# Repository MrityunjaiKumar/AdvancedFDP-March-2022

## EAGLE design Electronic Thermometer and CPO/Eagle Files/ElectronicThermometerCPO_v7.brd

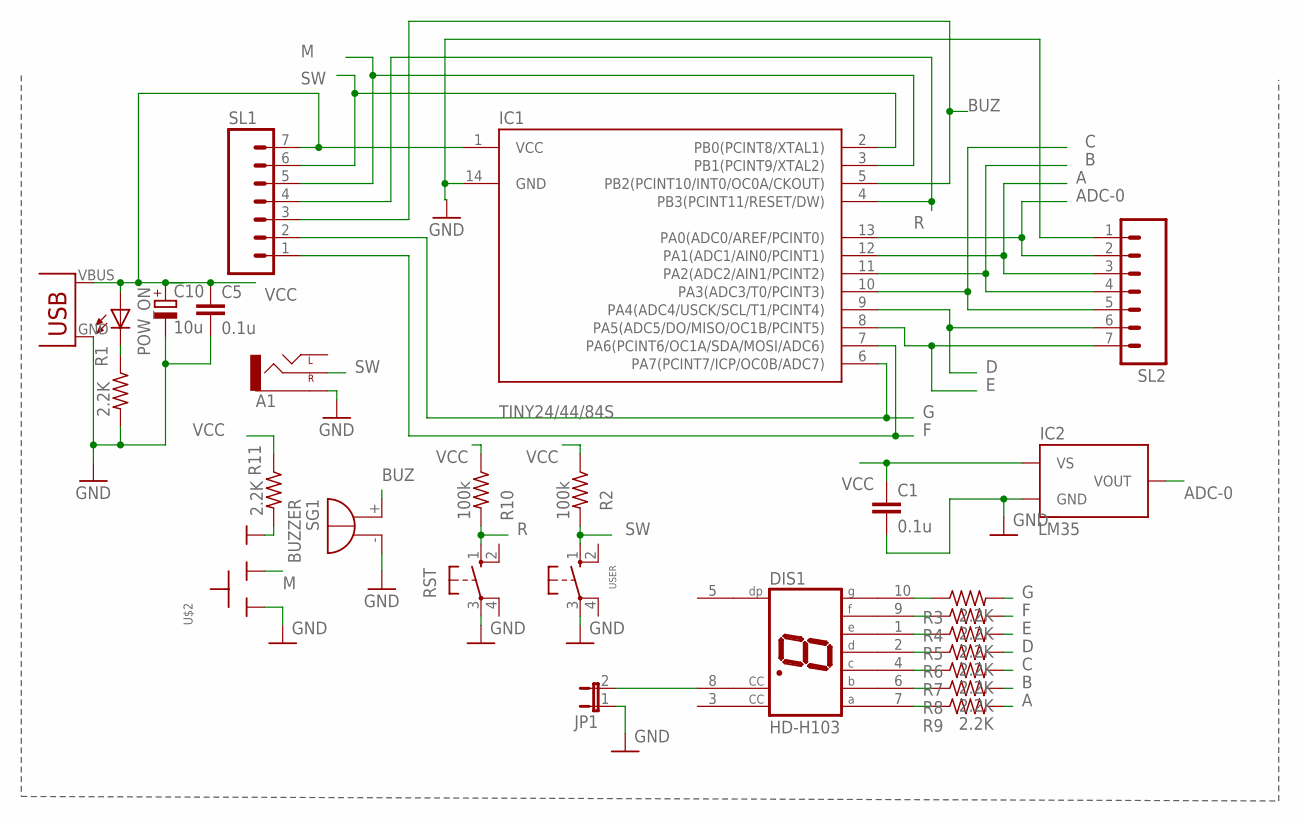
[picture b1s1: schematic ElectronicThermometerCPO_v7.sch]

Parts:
A1: AUDIO-JACKPTH; AUDIO-JACK
C1, C5: 0.1u; C0805
C10: 10u; B/3528-21R
DIS1: HD-H103; HDSP-M
IC1: TINY24/44/84S; SOIC14
IC2: LM35; TO92
JP1: JP1E; JP1
POW_ON: LED3MM
R1, R3, R4, R5, R6, R7, R8, R9, R11: 2.2K; 0207/10
R2, R10: 100k; 0207/10
RST: 10-XX; B3F-10XX
SG1: BUZZER; F/TMB
SL1, SL2: M07; 07P
U$1: USB(POWER)
U$2: SLIDESWITCH-BIG; BIGSWITCH
USER: 40-XX; B3F-40XX

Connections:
A: IC1.12 (PA1(ADC1/AIN0/PCINT1)), R9.2, SL2.3
ADC-0: IC1.13 (PA0(ADC0/AREF/PCINT0)), IC2.VOUT, SL2.2
B: IC1.11 (PA2(ADC2/AIN1/PCINT2)), R8.2, SL2.4
BUZ: IC1.5 (PB2(PCINT10/INT0/OC0A/CKOUT)), SG1.+, SL1.3
C: IC1.10 (PA3(ADC3/T0/PCINT3)), R7.2, SL2.5
D: IC1.9 (PA4(ADC4/USCK/SCL/T1/PCINT4)), R6.2, SL2.6
E: IC1.8 (PA5(ADC5/DO/MISO/OC1B/PCINT5)), R5.2, SL2.7
F: IC1.7 (PA6(PCINT6/OC1A/SDA/MOSI/ADC6)), R4.2, SL1.1
G: IC1.6 (PA7(PCINT7/ICP/OC0B/ADC7)), R3.2, SL1.2
GND: A1.SLEEVE, C1.2, C5.2, C10.-, IC1.14 (GND), IC2.GND, JP1.1, R1.2, RST.3, SG1.-, SL2.1, U$1.GND, U$2.1, USER.3
M: IC1.3 (PB1(PCINT9/XTAL2)), SL1.5, U$2.2
unnamed: POW_ON.K (C), R1.1
unnamed: DIS1.8 (CC), JP1.2
unnamed: DIS1.10 (G), R3.1
unnamed: DIS1.9 (F), R4.1
unnamed: R11.2, U$2.3
unnamed: DIS1.1 (E), R5.1
unnamed: DIS1.2 (D), R6.1
unnamed: DIS1.4 (C), R7.1
unnamed: DIS1.6 (B), R8.1
unnamed: DIS1.7 (A), R9.1
R: IC1.4 (PB3(PCINT11/RESET/DW)), R10.2, RST.1 (S), SL1.4
SW: A1.RING (RIGHT), IC1.2 (PB0(PCINT8/XTAL1)), R2.2, SL1.6, USER.1 (S)
VCC: C1.1, C5.1, C10.+, IC1.1 (VCC), IC2.VS, POW_ON.A, R2.1, R10.1, R11.1, SL1.7, U$1.VBUS (VCC)

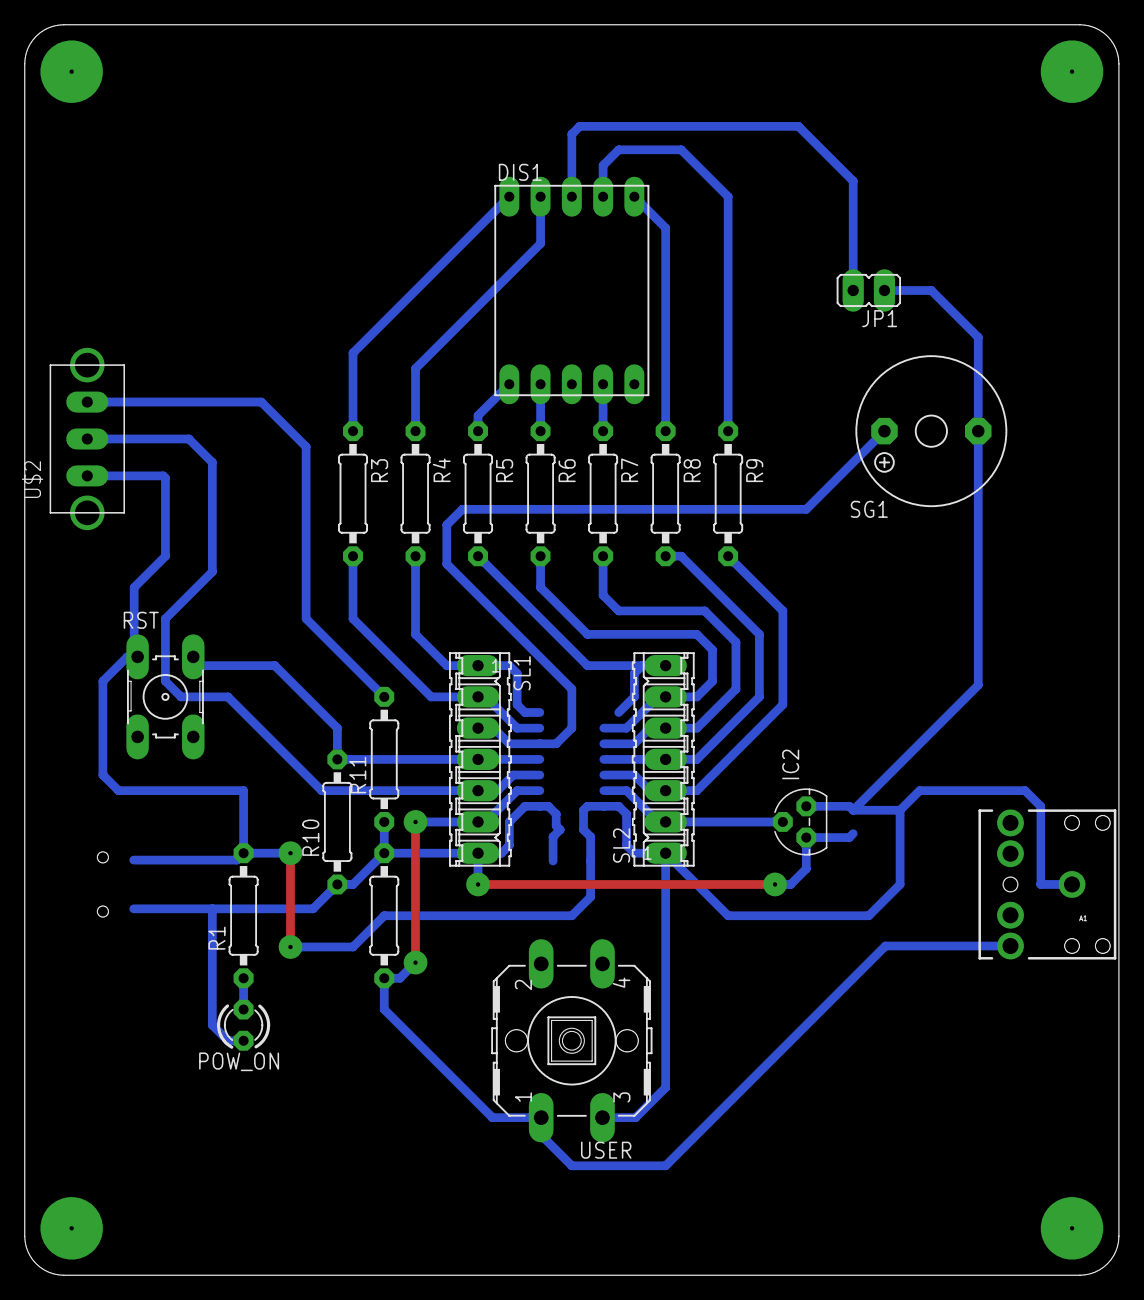
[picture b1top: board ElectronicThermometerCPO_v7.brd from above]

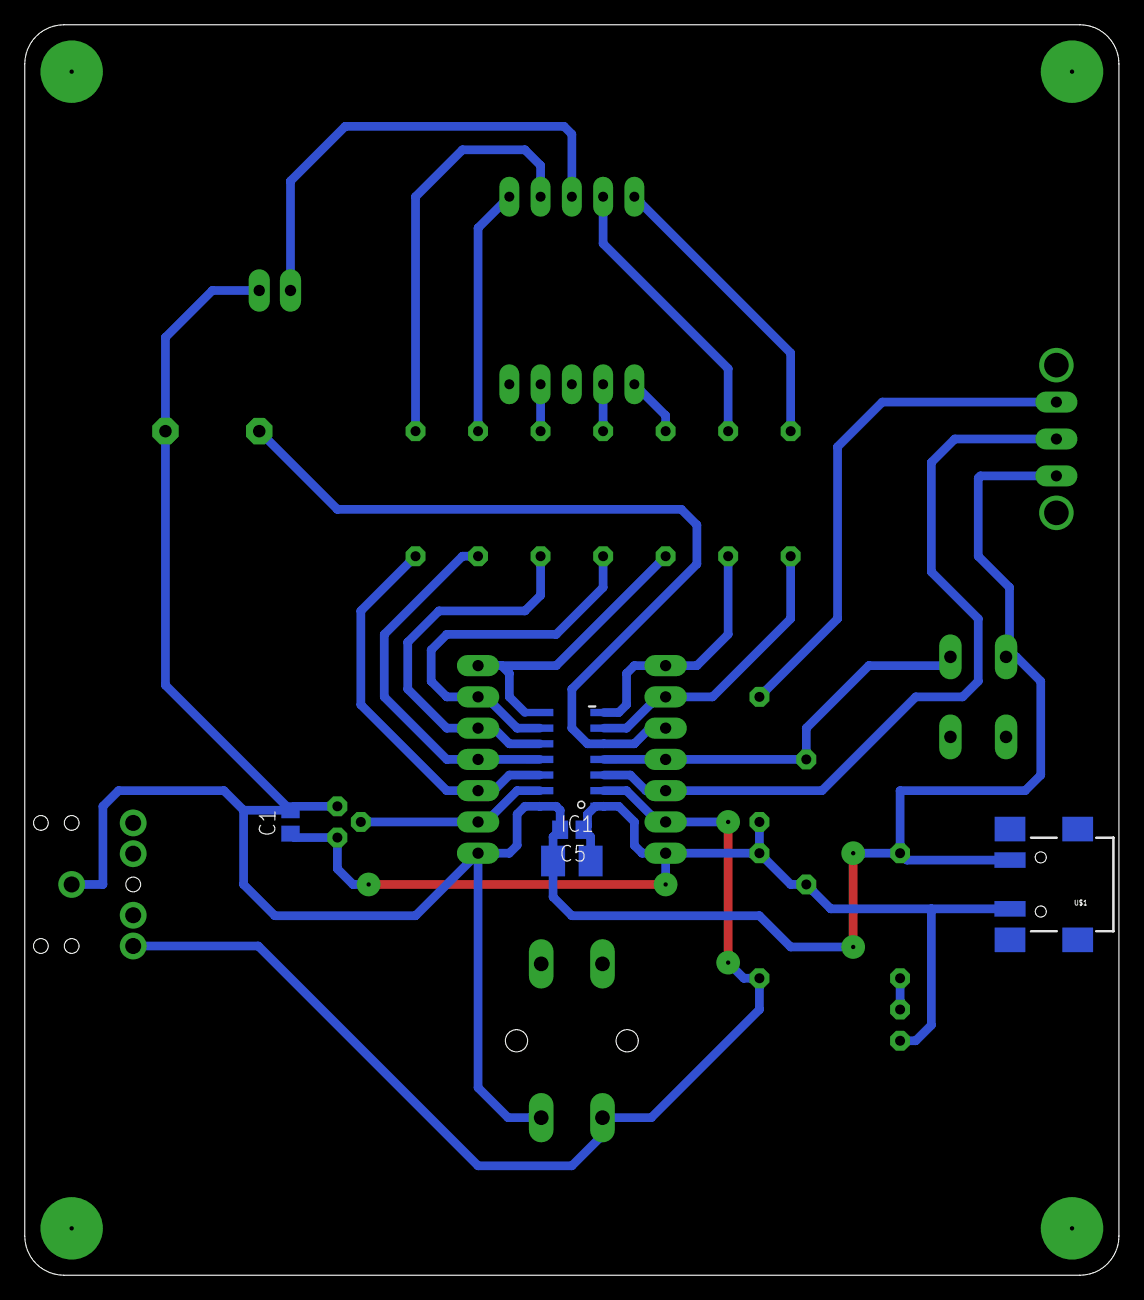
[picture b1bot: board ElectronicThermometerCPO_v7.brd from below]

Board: 2 copper layers, 88.9 x 101.6 mm, 27 parts (5 on the bottom side), 24 nets.

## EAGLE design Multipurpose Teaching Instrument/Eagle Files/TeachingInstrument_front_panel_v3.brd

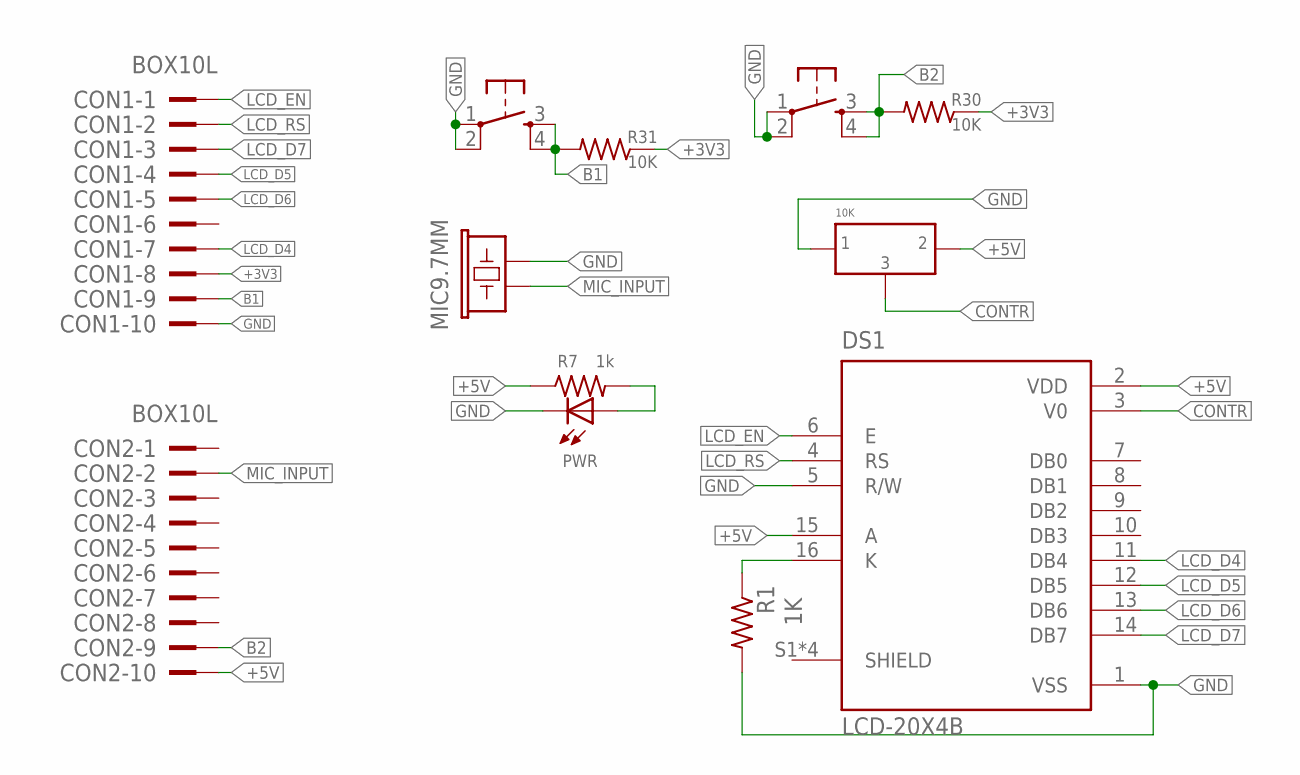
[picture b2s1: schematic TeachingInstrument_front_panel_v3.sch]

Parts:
CON1, CON2: BOX10L
DS1: LCD-20X4B; LCD_LCD-20X4B
PRESET: 10K; PRESET_LR
PWR: LED3MM
R1: 1K; 0207/10
R7: 1k; 0207/10
R30, R31: 10K; 0207/10
U$1, U$2: OMRON_SWITCH_40-XX; B3F-40XX
U$12: MIC9.7MM; MIC-9.7MM

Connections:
+3V3: CON1.8, R30.1, R31.1
+5V: CON2.10, DS1.2 (VDD), DS1.15 (A), PRESET.P$2 (2), R7.1
B1: CON1.9, R31.2, U$1.3 (S), U$1.4 (S1)
B2: CON2.9, R30.2, U$2.3 (S), U$2.4 (S1)
CONTR: DS1.3 (V0), PRESET.P$3 (3)
GND: CON1.10, DS1.1 (VSS), DS1.5 (R/W), PRESET.P$1 (1), PWR.K (C), R1.2, U$1.1, U$1.2 (P1), U$2.1, U$2.2 (P1), U$12.2
LCD_D4: CON1.7, DS1.11 (DB4)
LCD_D5: CON1.4, DS1.12 (DB5)
LCD_D6: CON1.5, DS1.13 (DB6)
LCD_D7: CON1.3, DS1.14 (DB7)
LCD_EN: CON1.1, DS1.6 (E)
LCD_RS: CON1.2, DS1.4 (RS)
MIC_INPUT: CON2.2, U$12.1
unnamed: DS1.16 (K), R1.1
unnamed: PWR.A, R7.2

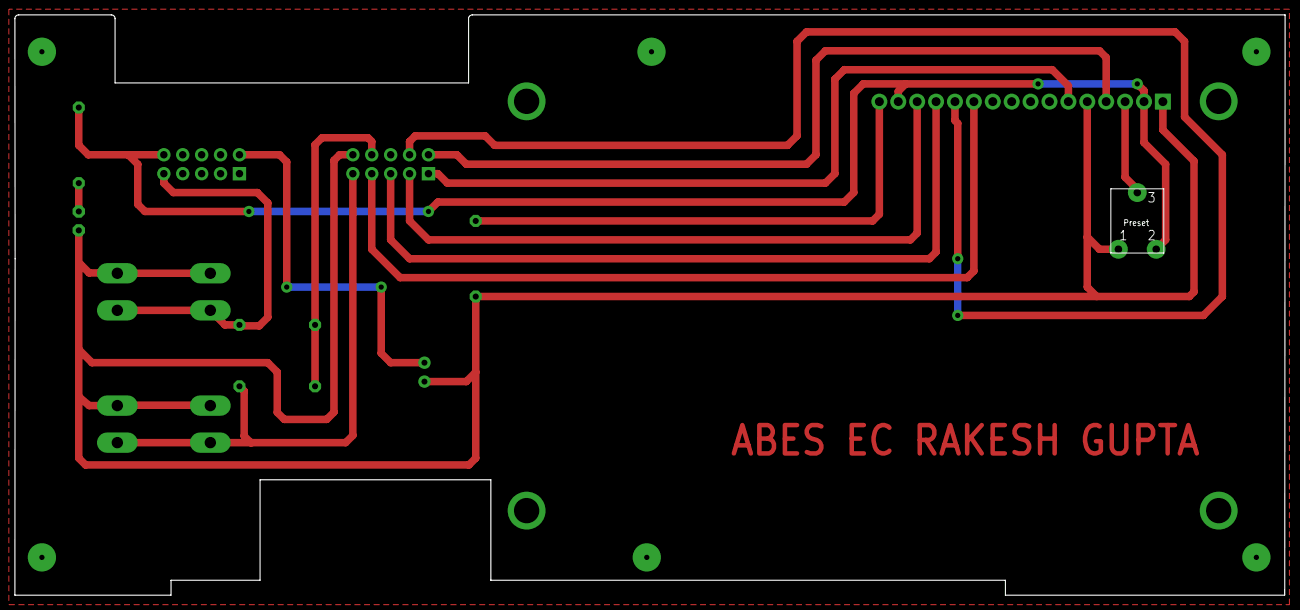
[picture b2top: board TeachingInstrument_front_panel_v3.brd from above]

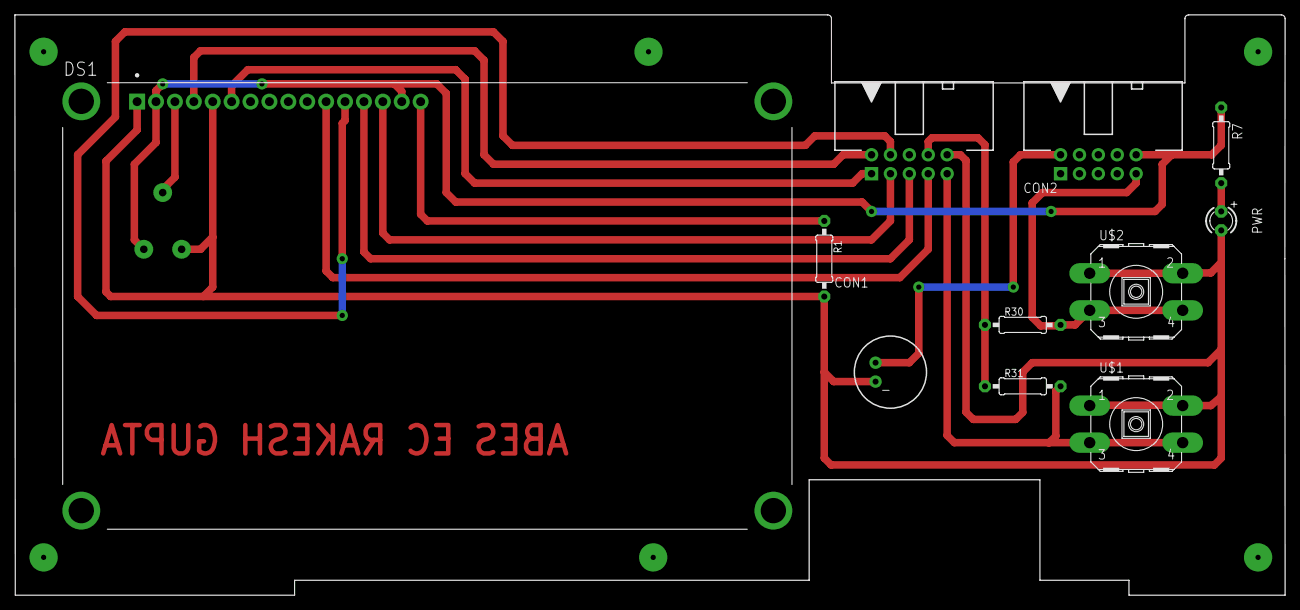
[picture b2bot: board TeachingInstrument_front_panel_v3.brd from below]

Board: 2 copper layers, 170.7 x 78.0 mm, 12 parts (11 on the bottom side), 15 nets.

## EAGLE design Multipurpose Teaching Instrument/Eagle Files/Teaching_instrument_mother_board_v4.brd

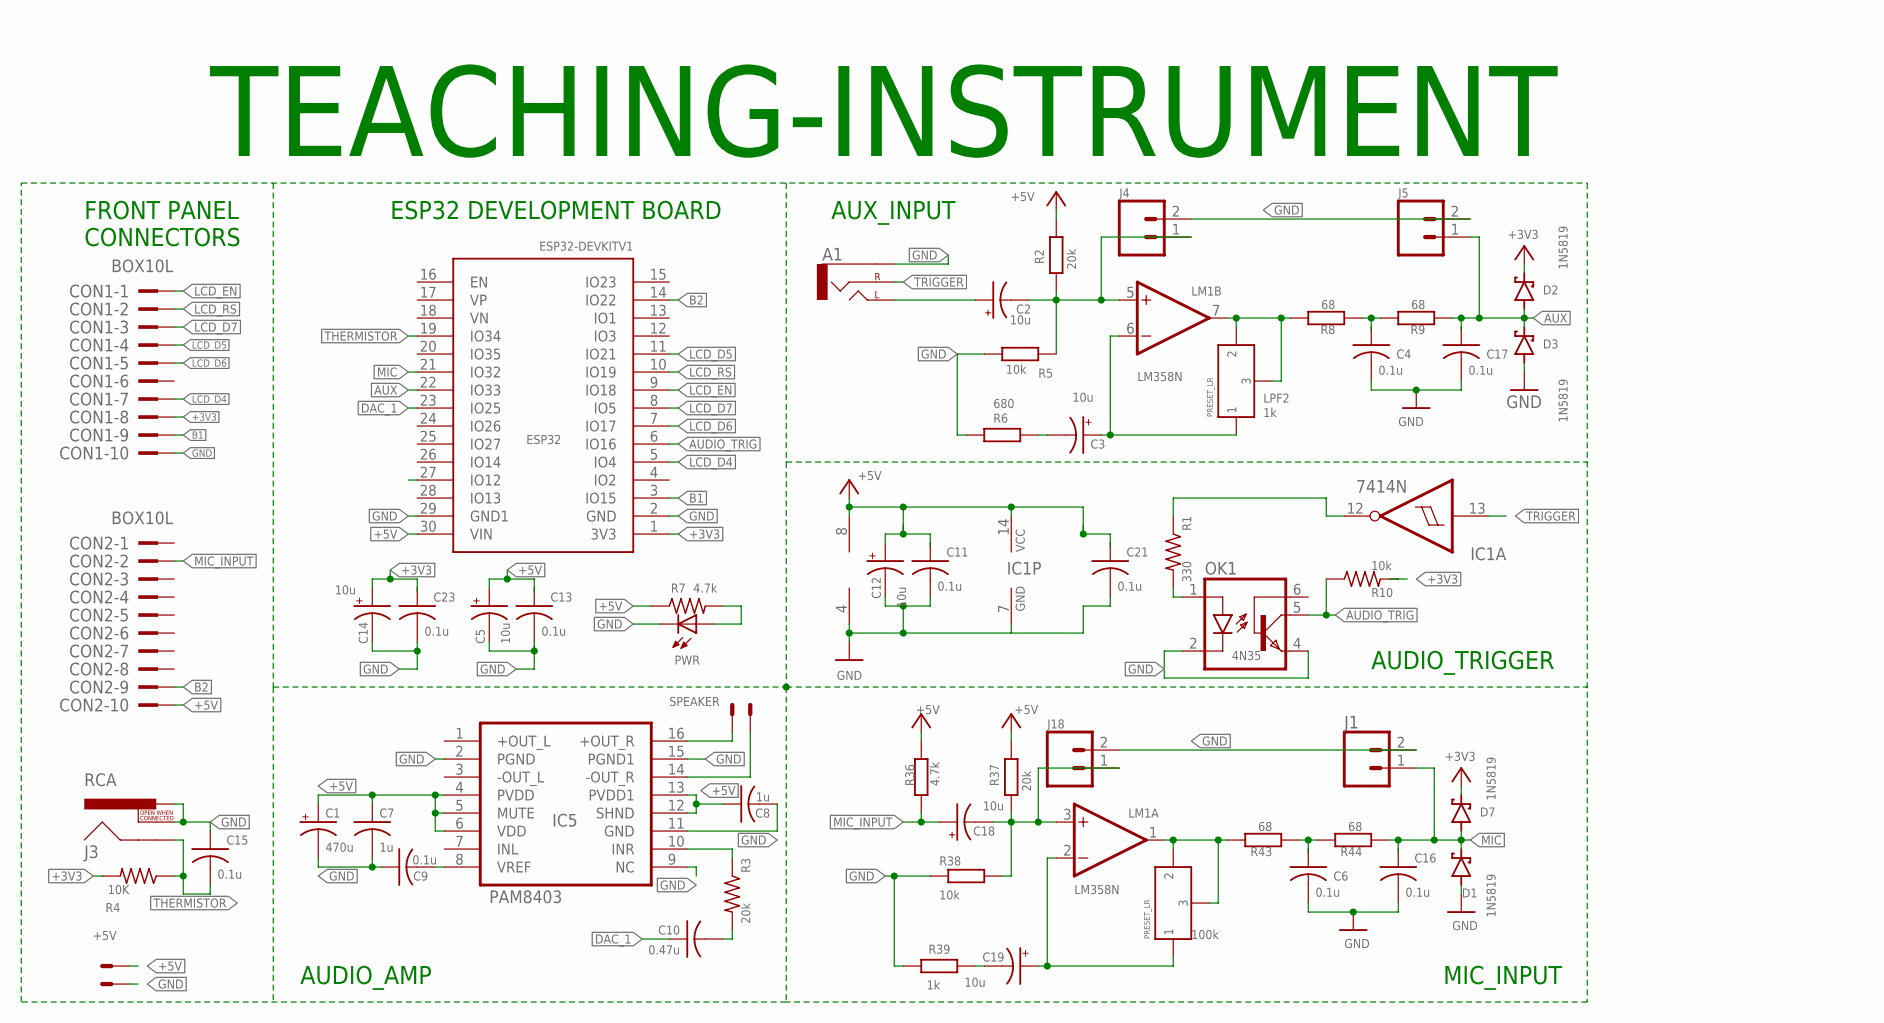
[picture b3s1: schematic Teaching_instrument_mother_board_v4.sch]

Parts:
100K: PRESET_LR
A1: CEDT_JANUARY_2015_V5_AUDIO-JACKPTH; CEDT_JANUARY_2015_V5_AUDIO-JACK
C1: 470u; E5-10,5
C2, C3, C5, C12, C14, C18, C19: 10u; E2,5-5
C4, C6, C11, C13, C15, C16, C17, C21, C23: 0.1u; C025-024X044
C7, C8: 1u; C0805
C9: 0.1u; C0805
C10: 0.47u; C0603
CON1, CON2: BOX10L
D1, D2, D3, D7: 1N5819; DO41-7.6
ESP32: ESP32-DEVKITV1_ESP32DEVKITV1ESP32; ESP32
IC1: 7414N; DIL14
IC5: PAM8403; SOP-16
J1, J4, J5, J18: CONN_02; 1X02
J3: RCA
LM1: LM358N; DIL08
OK1: 4N35; DIL06
PWR: LED3MM
R1: 330; M0805
R2, R3, R37: 20k; 0207/10
R4: 10K; 0207/10
R5, R38: 10k; 0207/10
R6: 680; 0207/10
R7, R36: 4.7k; 0207/10
R8, R9, R43, R44: 68; 0207/10
R10: 10k; M0805
R39: 1k; 0207/10
SPEAKER: SPEAKER; JST-XH-02-PACKAGE-LONG-PAD
U$3: PRESET_LR
X1: +5V; JST-XH-02-PACKAGE-LONG-PAD

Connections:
+3V3: C14.+, C23.1, CON1.8, D2.C, D7.C, ESP32.1 (3V3), R4.2, R10.2
+5V: C1.+, C5.+, C7.1, C8.1, C11.1, C12.+, C13.1, C21.1, CON2.10, ESP32.30 (VIN), IC1.14 (VCC), IC5.4 (PVDD), IC5.5 (MUTE), IC5.6 (VDD), IC5.12 (SHND), IC5.13 (PVDD1), LM1.8 (V+), R2.2, R7.1, R36.2, R37.2, X1.2
ADC_6: ESP32.27 (IO12)
AUDIO_TRIG: ESP32.6 (IO16), OK1.5 (COL), R10.1
AUX: C17.1, D2.A, D3.C, ESP32.22 (IO33), J5.1, R9.1
B1: CON1.9, ESP32.3 (IO15)
B2: CON2.9, ESP32.14 (IO22)
DAC_1: C10.1, ESP32.23 (IO25)
GND: A1.SLEEVE, C1.-, C4.2, C5.-, C6.2, C7.2, C8.2, C9.1, C11.2, C12.-, C13.2, C14.-, C15.1, C16.2, C17.2, C21.2, C23.2, CON1.10, D1.A, D3.A, ESP32.2 (GND), ESP32.29 (GND1), IC1.7 (GND), IC5.2 (PGND), IC5.9 (NC), IC5.11 (GND), IC5.15 (PGND1), J1.2, J3.PIN, J3.SWITCH, J4.2, J5.2, J18.2, LM1.4 (V-), OK1.2 (C), OK1.4 (EMI), PWR.K (C), R5.1, R6.1, R38.1, R39.1, X1.1
LCD_D4: CON1.7, ESP32.5 (IO4)
LCD_D5: CON1.4, ESP32.11 (IO21)
LCD_D6: CON1.5, ESP32.7 (IO17)
LCD_D7: CON1.3, ESP32.8 (IO5)
LCD_EN: CON1.1, ESP32.9 (IO18)
LCD_RS: CON1.2, ESP32.10 (IO19)
LPF1: 100K.P$2 (2), 100K.P$3 (3), LM1.1 (OUT), R43.2
LPF2: LM1.7 (OUT), R8.2, U$3.P$2 (2), U$3.P$3 (3)
MIC: C16.1, D1.C, D7.A, ESP32.21 (IO32), J1.1, R44.1
MIC_INPUT: C18.+, CON2.2, R36.1
unnamed: IC5.16 (+OUT_R), SPEAKER.2
unnamed: 100K.P$1 (1), C19.+, LM1.2 (-IN)
unnamed: A1.TIP (LEFT), C2.+
unnamed: OK1.1 (A), R1.2
unnamed: IC5.14 (-OUT_R), SPEAKER.1
unnamed: C3.-, R6.2
unnamed: C9.2, IC5.8 (VREF)
unnamed: C10.2, R3.2
unnamed: C2.-, J4.1, LM1.5 (+IN), R2.1, R5.2
unnamed: C3.+, LM1.6 (-IN), U$3.P$1 (1)
unnamed: IC1.12 (O), R1.1
unnamed: C4.1, R8.1, R9.2
unnamed: IC5.10 (INR), R3.1
unnamed: C6.1, R43.1, R44.2
unnamed: PWR.A, R7.2
unnamed: C19.-, R39.2
THERMISTOR: C15.2, ESP32.19 (IO34), J3.SHELL, R4.1
TRIGGER: A1.RING (RIGHT), IC1.13 (I)
V3: C18.-, J18.1, LM1.3 (+IN), R37.1, R38.2

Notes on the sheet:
100k
TEACHING-INSTRUMENT
ESP32 DEVELOPMENT BOARD
FRONT PANEL CONNECTORS
AUDIO_AMP
AUX_INPUT
AUDIO_TRIGGER
MIC_INPUT

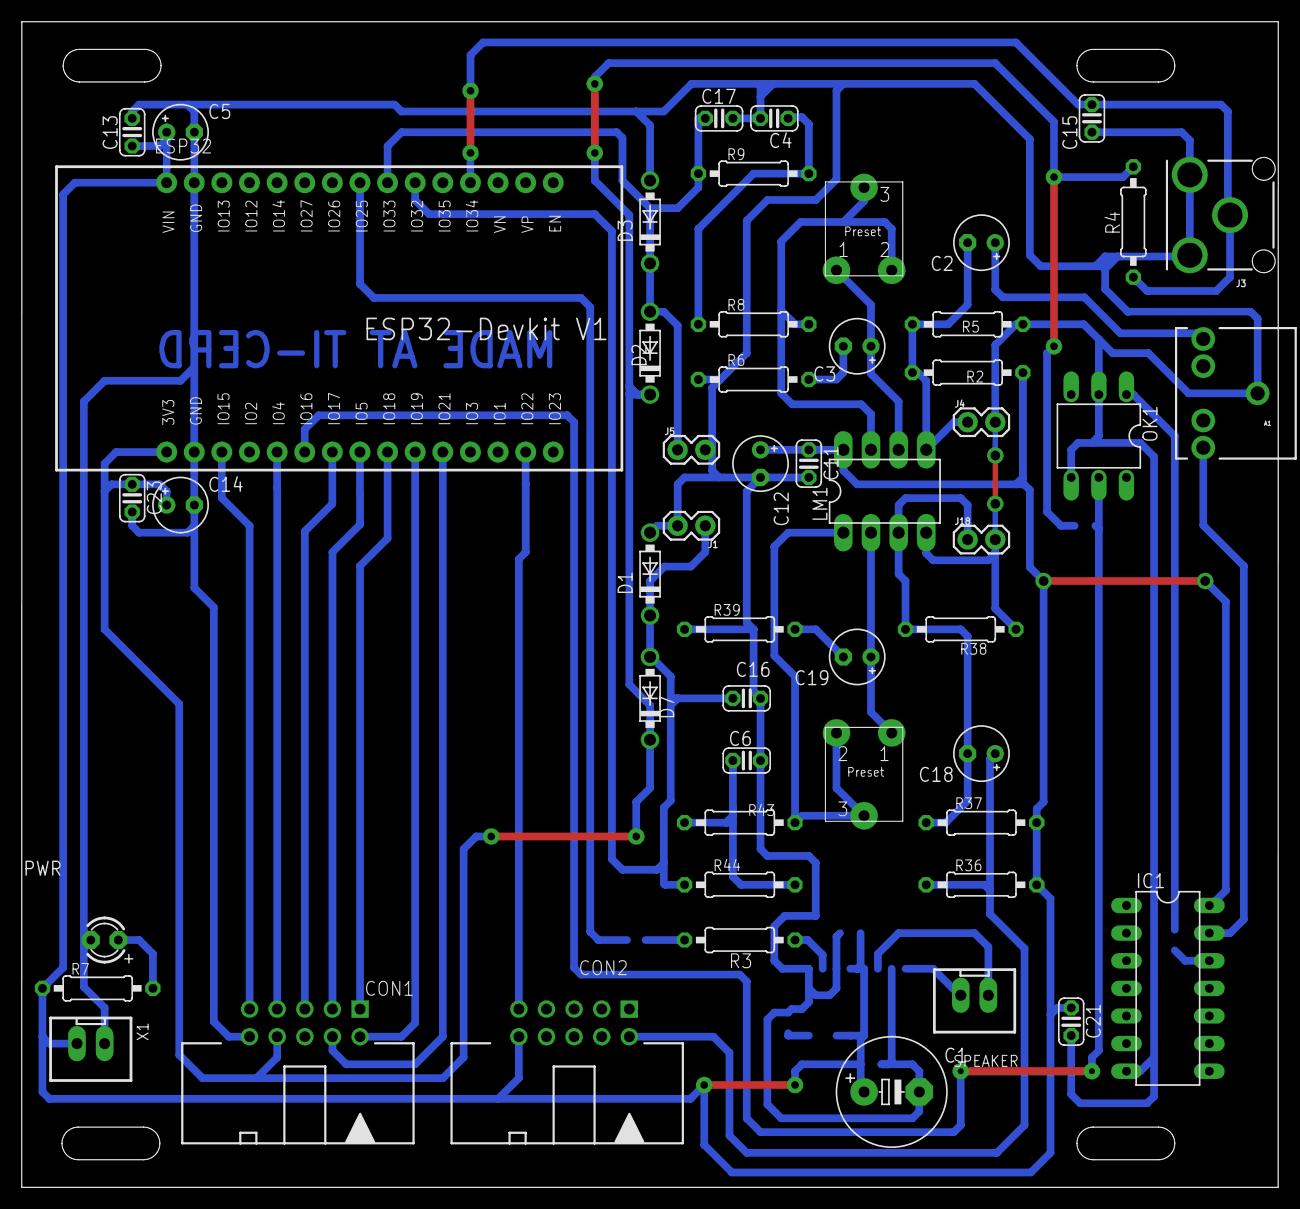
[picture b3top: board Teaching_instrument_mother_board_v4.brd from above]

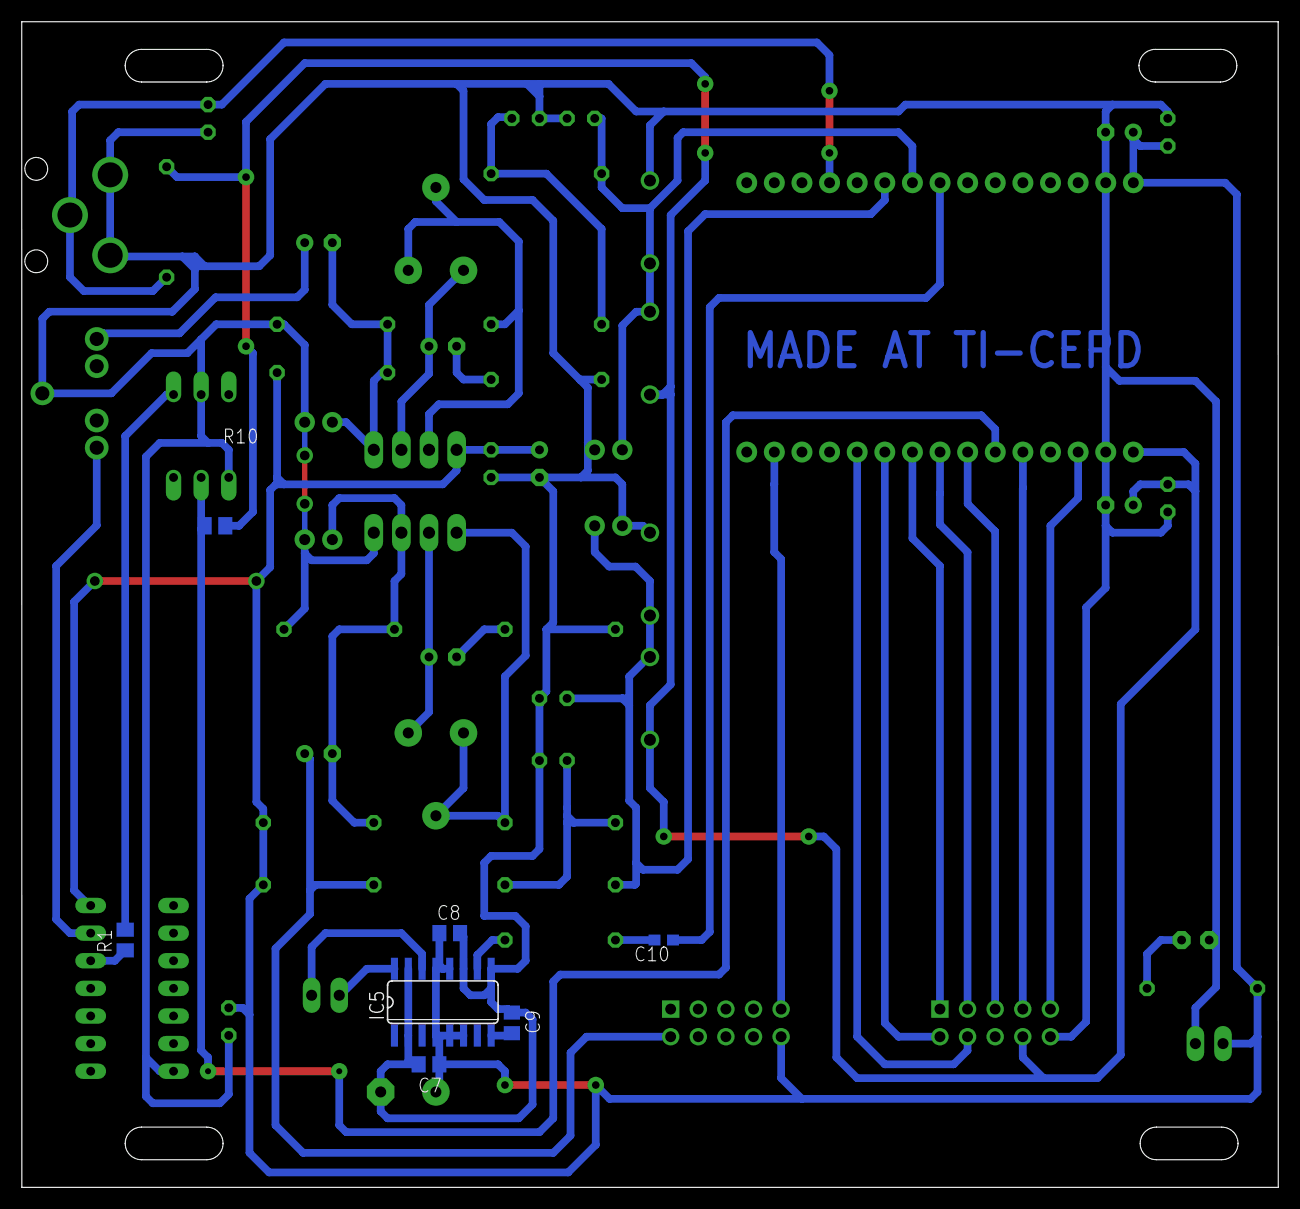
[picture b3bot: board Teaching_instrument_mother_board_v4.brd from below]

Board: 2 copper layers, 115.6 x 107.2 mm, 59 parts (7 on the bottom side), 37 nets.

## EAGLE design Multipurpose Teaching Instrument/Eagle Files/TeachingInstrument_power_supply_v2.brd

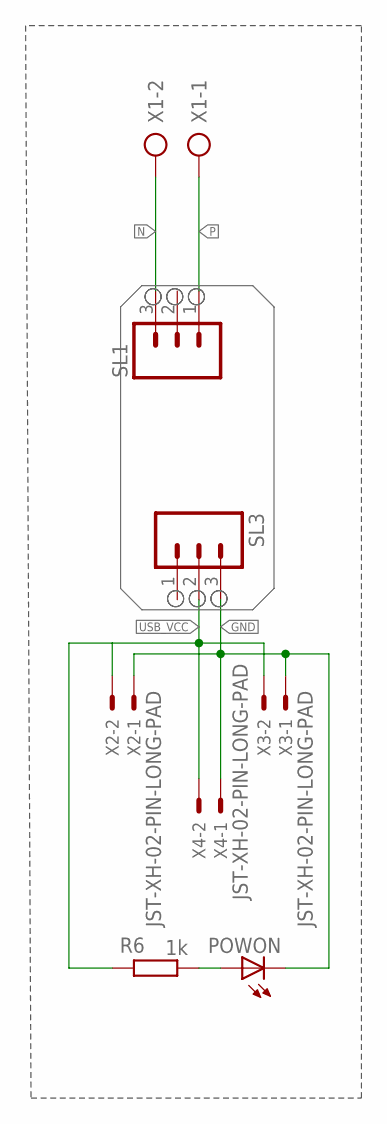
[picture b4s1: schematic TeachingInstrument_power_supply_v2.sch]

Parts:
POWON: LED3MM
R6: 1k; 0204/7
SL1, SL3: M03; 03P
X1: AK500/2-H
X2, X3, X4: JST-XH-02-PIN-LONG-PAD; JST-XH-02-PACKAGE-LONG-PAD

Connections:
GND: POWON.K (C), SL3.3, X2.1, X3.1, X4.1
N: SL1.3, X1.2
unnamed: POWON.A, R6.1
P: SL1.1, X1.1
USB_VCC: R6.2, SL3.2, X2.2, X3.2, X4.2

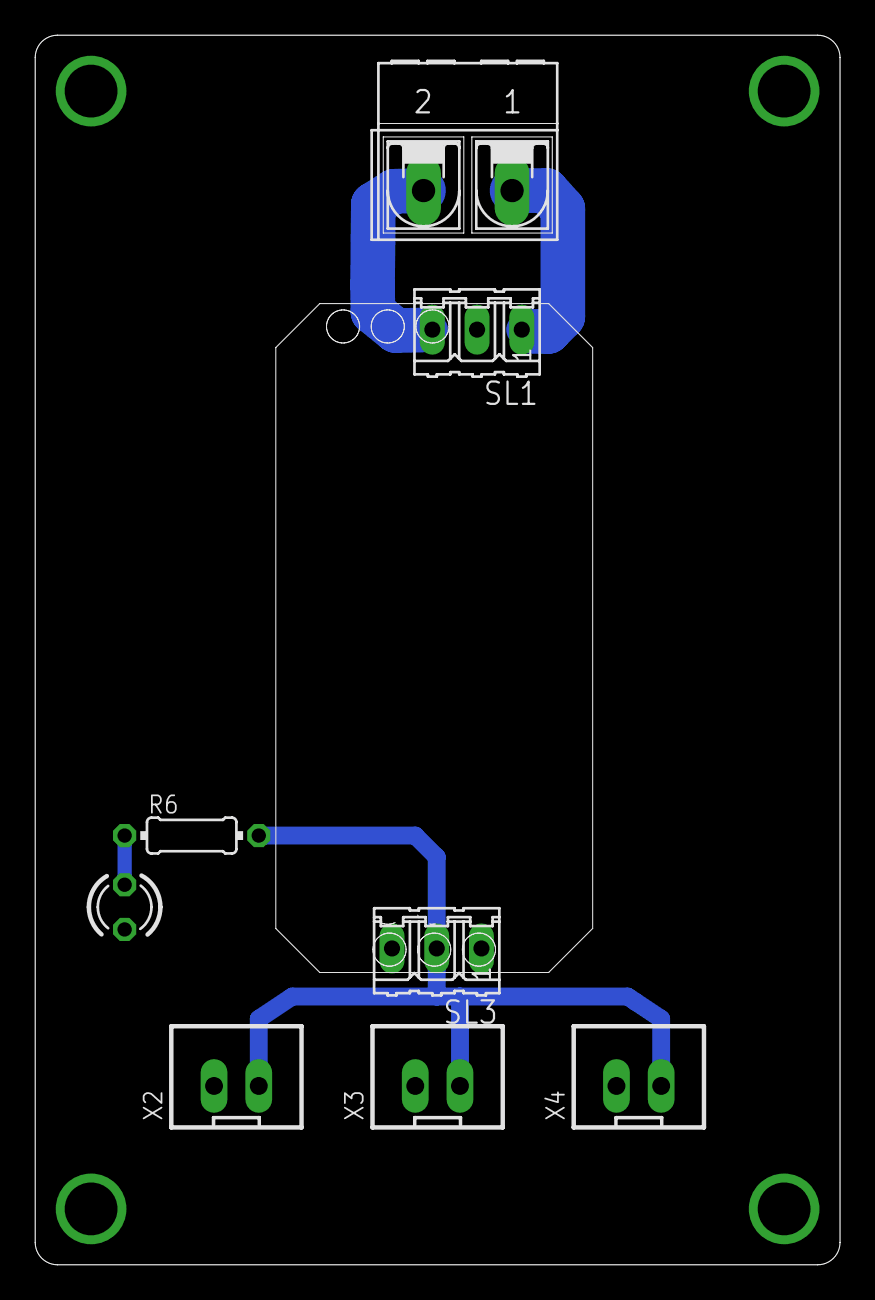
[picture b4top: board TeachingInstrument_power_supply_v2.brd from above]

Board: 2 copper layers, 45.7 x 69.8 mm, 8 parts (0 on the bottom side), 5 nets.

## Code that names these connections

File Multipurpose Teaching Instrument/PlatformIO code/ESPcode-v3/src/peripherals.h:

#define LCD_RESET_PIN 19 
#define LCD_ENABLE_PIN 18
#define LCD_DATA_PIN4 4
#define LCD_DATA_PIN5 21
#define LCD_DATA_PIN6 17
#define LCD_DATA_PIN7 5
#define aux 33
#define mic 32
#define up 22
#define down 15
#define thermistor 34
#define aud_trig 16

//talkative tom
uint16_t fft_fs_tt = 20000;
const int32_t max_size_tt = 55000;
byte buff[max_size_tt] = { 0 };
int i_tt, rec_index_tt = 0;
float current_ip_tt = 0;
float previous_ip_tt = 0;
float lambda_tt = 0.01; //0.017
uint8_t val_tt = 0;
//
bool mic_aux = false;
bool curr_state = 0;
bool prev_state = 0;
long randNumber;
bool sensor_nc = false;
long unsigned int longp = 0;
uint8_t screen = 0;
int display_xy[4][128] = { 0 };
volatile uint16_t adc_reading = 0;
static const adc1_channel_t ADC_channel = ADC1_CHANNEL_5;
static const adc1_channel_t ADC_channel_2 = ADC1_CHANNEL_4;
uint16_t point = 0;
volatile bool cnt = false;
const uint16_t fft_max_size = 256;
uint16_t fft_size = 256;
int length_r = (fft_size / 2) + 1;
uint16_t fft_fs = 40000;
float fft_in[fft_max_size], samples_abs[fft_max_size], samples_norm[fft_max_size] = { 0 };
float temp_real, temp_imag;
int steps, lower, upper, skip;
struct complex {
  float real, imag;
};
struct complex twiddle[fft_max_size >> 1];
struct complex samples[fft_max_size] = {};
int bit_reverse[fft_max_size];
uint16_t i, j;
enum location { HOME_TEMP, MIC_FFT, AUX_FFT, LOON, TALKING_TOM, RADIO, BLUETOOTH};
location current_location = HOME_TEMP;
float R2 = 10000;
float logR1, R1;
float temp, tempF = 0;
float c1 = 0.001125308852122;
float c2 = 0.000234711863267;
float c3 = 0.000000085663516;
float temperature = 0;
uint16_t delay_to_switch = 2000;
uint16_t wifi_timeout = 30000;

float to_temperature() {
  temp = 0;
  sensor_nc = false;
  for (int i = 0; i < 256;i++) {
    temp = temp + analogRead(thermistor);
  }
  temp = temp / 256;
  if (temp > 3900) {
    sensor_nc = true;
  }
  R1 = R2 / ((4096 / (float)temp) - 1);
  logR1 = log(R1);
  tempF = (1.0 / (c1 + c2 * logR1 + c3 * logR1 * logR1 * logR1));
  tempF = tempF - 273.15;
  return tempF;
}

LiquidCrystal lcd(LCD_RESET_PIN, LCD_ENABLE_PIN, LCD_DATA_PIN4, LCD_DATA_PIN5, LCD_DATA_PIN6, LCD_DATA_PIN7);

byte a[] = {
  B00000,
  B00000,
  B00000,
  B00000,
  B00000,
  B00000,
  B00000,
  B11111,
};
byte b[] = {
  B00000,
  B00000,
  B00000,
  B00000,
  B00000,
  B00000,
  B11111,
  B11111,
};
byte c[] = {
  B00000,
  B00000,
  B00000,
  B00000,
  B00000,
  B11111,
  B11111,
  B11111,
};
byte d[] = {
  B00000,
  B00000,
  B00000,
  B00000,
  B11111,
  B11111,
  B11111,
  B11111,
};
byte e[] = {
  B00000,
  B00000,
  B00000,
  B11111,
  B11111,
  B11111,
  B11111,
  B11111,
};
byte f[] = {
  B00000,
  B00000,
  B11111,
  B11111,
  B11111,
  B11111,
  B11111,
  B11111,
};
byte g[] = {
  B00000,
  B11111,
  B11111,
  B11111,
  B11111,
  B11111,
  B11111,
  B11111,
};
byte h[] = {
  B11111,
  B11111,
  B11111,
  B11111,
  B11111,
  B11111,
  B11111,
  B11111,
};
void adc_init_aux() {
  pinMode(aux, INPUT);
  adcAttachPin(aux);
  analogSetAttenuation(ADC_11db);
  CLEAR_PERI_REG_MASK(SENS_SAR_MEAS_START1_REG, SENS_MEAS1_START_SAR_M);
  SET_PERI_REG_BITS(SENS_SAR_MEAS_START1_REG, SENS_SAR1_EN_PAD, (1 << ADC_channel), SENS_SAR1_EN_PAD_S);
}
void adc_init_mic() {
  pinMode(mic, INPUT);
  adcAttachPin(mic);
  analogSetAttenuation(ADC_11db);
  CLEAR_PERI_REG_MASK(SENS_SAR_MEAS_START1_REG, SENS_MEAS1_START_SAR_M);
  SET_PERI_REG_BITS(SENS_SAR_MEAS_START1_REG, SENS_SAR1_EN_PAD, (1 << ADC_channel_2), SENS_SAR1_EN_PAD_S);
}
void adc_read() {
  CLEAR_PERI_REG_MASK(SENS_SAR_MEAS_START1_REG, SENS_MEAS1_START_SAR_M);
  SET_PERI_REG_MASK(SENS_SAR_MEAS_START1_REG, SENS_MEAS1_START_SAR_M);
  while (GET_PERI_REG_MASK(SENS_SAR_MEAS_START1_REG, SENS_MEAS1_DONE_SAR) == 0);
  adc_reading = GET_PERI_REG_BITS2(SENS_SAR_MEAS_START1_REG, SENS_MEAS1_DATA_SAR, SENS_MEAS1_DATA_SAR_S);
}
void lcd_init() {
  lcd.begin(20, 4);
  lcd.clear();
  lcd.createChar(0, a);
  lcd.createChar(1, b);
  lcd.createChar(2, c);
  lcd.createChar(3, d);
  lcd.createChar(4, e);
  lcd.createChar(5, f);
  lcd.createChar(6, g);
  lcd.createChar(7, h);
}
void printStr(String text, int index, int line) {
  lcd.setCursor(index, line);
  lcd.print(text);
}

void printChr(int character, int index, int line) {
  lcd.setCursor(index, line);
  lcd.write(character);
}

void clearLine(int line) {
  lcd.setCursor(0, line);
  lcd.print("                    ");
}

void bitReverse(int* X, int M) {
  X[0] = 0;
  int i, j;
  for (i = M >> 1;i >= 1;i = i / 2) {
    for (j = 0;j < (M / i) >> 1;j++) {
      X[j + (M / (2 * i))] = X[j] + i;
    }
  }
}

void copy_array(struct complex* out, float* inp, int M) {
  for (i = 0;i < M / 2;i++) {
    out[i].real = inp[bit_reverse[i]];
    out[i + M / 2].real = inp[bit_reverse[i] + 1];
    out[i].imag = 0;
    out[i + M / 2].imag = 0;
  }
}
void fft(struct complex* Y, int M, struct complex* w) {
  steps = 1;
  do {
    steps *= 2;

    for (i = 0;i < M / steps;i++) {
      for (j = 0;j < steps / 2;j++) {
        lower = i * steps + j + steps / 2;
        upper = i * steps + j;
        skip = M * j / steps;

        temp_real = Y[lower].real * w[skip].real - Y[lower].imag * w[skip].imag;
        temp_imag = Y[lower].real * w[skip].imag + Y[lower].imag * w[skip].real;

        Y[lower].real = Y[upper].real - temp_real;
        Y[lower].imag = Y[upper].imag - temp_imag;
        Y[upper].real = Y[upper].real + temp_real;
        Y[upper].imag = Y[upper].imag + temp_imag;
      }
    }
  } while (steps != M);
}
void absolute(struct complex* inp, int M, float* out) {
  int i;
  for (i = 0;i < M;i++)
    out[i] = (inp[i].real * inp[i].real + inp[i].imag * inp[i].imag);
}
void normalize(float* input_abs_data) {
  float maximum_element = input_abs_data[0];
  for (int i = 1; i < fft_size; i++) {
    if (maximum_element < input_abs_data[i]) {
      maximum_element = input_abs_data[i];
    }
  }
  for (int i = 0; i < fft_size; i++) {
    input_abs_data[i] = input_abs_data[i] / maximum_element;
    input_abs_data[i] = int(32 * input_abs_data[i]);
  }
}
void fft_data() {
  copy_array(samples, fft_in, fft_size);
  fft(samples, fft_size, twiddle);
  absolute(samples, fft_size, samples_abs);
  normalize(samples_abs);
}

void twid(struct complex* Y, int M) {
  for (i = 0;i < M >> 1;i++) {
    Y[i].real = cos(2 * PI * i / M);
    Y[i].imag = sin(2 * PI * i / M);
  }
}

void display_data() {
  for (int k = 0; k < (fft_size / 2); k++) {
    int q, r = 0;
    q = int(samples_abs[k]) / 8;
    r = int(samples_abs[k]) % 8;
    if (q == 0) {
      display_xy[3][k] = r;
      display_xy[2][k] = 0;
      display_xy[1][k] = 0;
      display_xy[0][k] = 0;
    }
    else if (q == 1) {
      display_xy[3][k] = 8;
      display_xy[2][k] = r;
      display_xy[1][k] = 0;
      display_xy[0][k] = 0;
    }
    else if (q == 2) {
      display_xy[3][k] = 8;
      display_xy[2][k] = 8;
      display_xy[1][k] = r;
      display_xy[0][k] = 0;
    }
    else if (q == 3) {
      display_xy[3][k] = 8;
      display_xy[2][k] = 8;
      display_xy[1][k] = 8;
      display_xy[0][k] = r;
    }
    else if (q == 4) {
      display_xy[3][k] = 8;
      display_xy[2][k] = 8;
      display_xy[1][k] = 8;
      display_xy[0][k] = 8;
    }
  }
}
void dac_init() {
  pinMode(25, ANALOG);
  CLEAR_PERI_REG_MASK(SENS_SAR_DAC_CTRL1_REG, SENS_SW_TONE_EN);
  CLEAR_PERI_REG_MASK(SENS_SAR_DAC_CTRL2_REG, SENS_DAC_CW_EN1_M);
  SET_PERI_REG_MASK(RTC_IO_PAD_DAC1_REG, RTC_IO_PDAC1_XPD_DAC | RTC_IO_PDAC1_DAC_XPD_FORCE);
}

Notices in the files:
parts and their libraries:
SparkFun-Connectors: Licensing: Creative Commons ShareAlike 4.0 International - https://creativecommons.org/licenses/by-sa/4.0
